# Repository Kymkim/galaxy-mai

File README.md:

# galaxy-mai

This project aims to create a AstroDx controller for the Samsung Galaxy Tab

Cooking in progress! Here are some devlogs!

## 01/01/2026: My 3D printer is back!
Few weeks ago I broke my printer so I had to postpone this project for some weeks. I got a new one now so I should be able to hop back into action. Right now I'm in the process of designining the case. Since the design is pretty much constraied by size, I had to draft the case first to get a better idea on how much space I can have once I start putting down the parts in. 

I'm thinking of creating a PCB for this design and some Khail hotswap sockets. They are easy enough to source and should be low profile enough so it looks somewhat proportional to the actual cab. Yes the PCB of course will add up to the overall cost if someone needs to build this instead of just using generic Omron switches - but my reasoning to this is that I want this to be as compact and integrated as possible. 

The schematic and the code of this project is very basic and pretty much just a simple keyboard hid. I have bunch of codes that I have made prior to this project that should let me just reuse the same code and call it the day.

Anyways, I'll keep working on the case and hopefully get something finished and done in one or two weeks

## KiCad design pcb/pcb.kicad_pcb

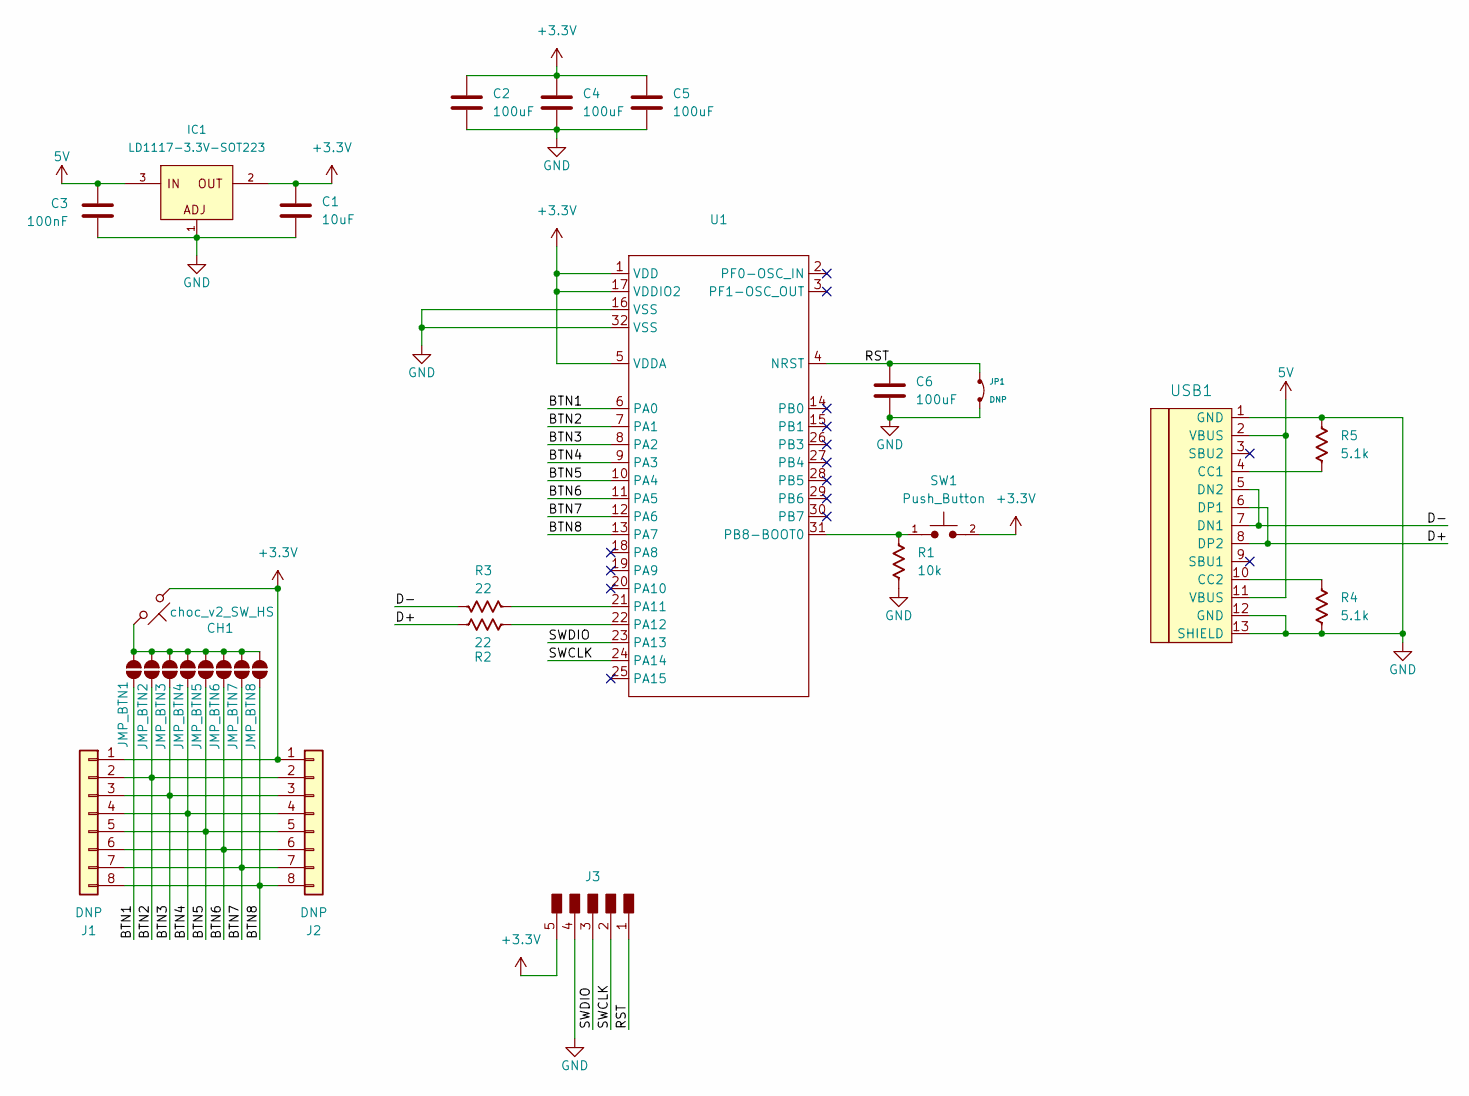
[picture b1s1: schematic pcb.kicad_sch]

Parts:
C1: 10uF; C_0805_2012Metric
C2, C4, C5, C6: 100uF; C_0805_2012Metric
C3: 100nF; C_0805_2012Metric
CH1: choc_v2_SW_HS; SW_Hotswap_Kailh_Choc_V1V2
IC1: LD1117-3.3V-SOT223; SOT223; Part Number LD1117S33CTR
J1, J2: DNP; 1x08_P2.54mm
J3: DNP; PinHeader_01x05_P2.54mm_Vertical_THT_D1.4mm
JMP_BTN1, JMP_BTN2, JMP_BTN3, JMP_BTN4, JMP_BTN5, JMP_BTN6, JMP_BTN7, JMP_BTN8: Jumper_2_NO_NoSilk
JP1: DNP; JUP_P5.08mm
R1: 10k; R_0805_2012Metric
R2, R3: 22; R_0805_2012Metric
R4, R5: 5.1k; R_0805_2012Metric
SW1: Push_Button; SW_PUSH_6mm
U1: LQFP-32_7x7mm_P0.8mm
USB1: HRO-TYPE-C-31-M-12; HRO-TYPE-C-31-M-12-HandSoldering

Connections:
5V: C3.1, IC1.3 (IN), USB1.2 (VBUS), USB1.11 (VBUS)
+3.3V: C1.2, C2.2, C4.2, C5.2, CH1.2, IC1.2 (OUT), J1.1, J2.1, J3.5, SW1.2, U1.1 (VDD), U1.5 (VDDA), U1.17 (VDDIO2); also elsewhere on the board
/BTN1: JMP_BTN1.2 (B), U1.6 (PA0); also elsewhere on the board
/BTN2: J1.2, J2.2, JMP_BTN2.1 (A), U1.7 (PA1); also elsewhere on the board
/BTN3: J1.3, J2.3, JMP_BTN3.1 (A), U1.8 (PA2); also elsewhere on the board
/BTN4: J1.4, J2.4, JMP_BTN4.1 (A), U1.9 (PA3); also elsewhere on the board
/BTN5: J1.5, J2.5, JMP_BTN5.1 (A), U1.10 (PA4); also elsewhere on the board
/BTN6: J1.6, J2.6, JMP_BTN6.1 (A), U1.11 (PA5); also elsewhere on the board
/BTN7: J1.7, J2.7, JMP_BTN7.1 (A), U1.12 (PA6); also elsewhere on the board
/BTN8: J1.8, J2.8, JMP_BTN8.1 (A), U1.13 (PA7); also elsewhere on the board
/D+: R2.1, USB1.6 (DP1), USB1.8 (DP2)
/D-: R3.1, USB1.5 (DN2), USB1.7 (DN1)
/RST: C6.2, J3.1, JP1.1, U1.4 (NRST); also elsewhere on the board
/SWCLK: J3.2, U1.24 (PA14); also elsewhere on the board
/SWDIO: J3.3, U1.23 (PA13); also elsewhere on the board
GND: C1.1, C2.1, C3.2, C4.1, C5.1, C6.1, IC1.1 (ADJ), J3.4, JP1.2, R1.1, R4.2, R5.1, U1.16 (VSS), U1.32 (VSS), USB1.1 (GND), USB1.12 (GND), USB1.13 (SHIELD); also elsewhere on the board
unnamed: CH1.1, JMP_BTN1.1 (A), JMP_BTN2.2 (B), JMP_BTN3.2 (B), JMP_BTN4.2 (B), JMP_BTN5.2 (B), JMP_BTN6.2 (B), JMP_BTN7.2 (B), JMP_BTN8.2 (B)
unnamed 17: R3.2, U1.21 (PA11); also elsewhere on the board
unnamed 18: R2.2, U1.22 (PA12); also elsewhere on the board
unnamed 19: R1.2, SW1.1, U1.31 (PB8-BOOT0); also elsewhere on the board
unnamed: R5.2, USB1.4 (CC1)
unnamed: R4.1, USB1.10 (CC2)

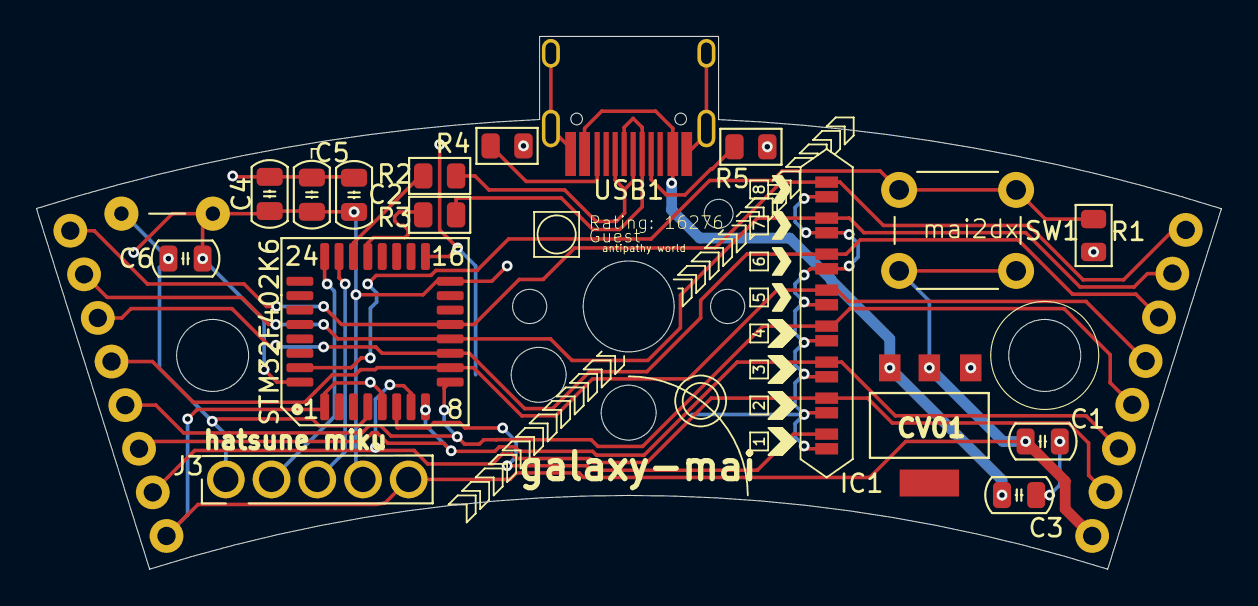
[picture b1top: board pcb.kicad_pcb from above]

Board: 2 copper layers, 65.8 x 29.6 mm, 28 parts (0 on the bottom side), 22 nets.

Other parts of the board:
STM32F402K6: LQFP-32_7x7mm_P0.8mm

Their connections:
+3.3V: STM32F402K6.1 (VDD), STM32F402K6.5 (VDDA), STM32F402K6.17 (VDDIO2); also elsewhere on the board
/BTN1: STM32F402K6.6 (PA0); also elsewhere on the board
/BTN2: STM32F402K6.7 (PA1); also elsewhere on the board
/BTN3: STM32F402K6.8 (PA2); also elsewhere on the board
/BTN4: STM32F402K6.9 (PA3); also elsewhere on the board
/BTN5: STM32F402K6.10 (PA4); also elsewhere on the board
/BTN6: STM32F402K6.11 (PA5); also elsewhere on the board
/BTN7: STM32F402K6.12 (PA6); also elsewhere on the board
/BTN8: STM32F402K6.13 (PA7); also elsewhere on the board
/RST: STM32F402K6.4 (NRST); also elsewhere on the board
/SWCLK: STM32F402K6.24 (PA14); also elsewhere on the board
/SWDIO: STM32F402K6.23 (PA13); also elsewhere on the board
GND: STM32F402K6.16 (VSS), STM32F402K6.32 (VSS); also elsewhere on the board
unnamed 17: STM32F402K6.21 (PA11); also elsewhere on the board
unnamed 18: STM32F402K6.22 (PA12); also elsewhere on the board
unnamed 19: STM32F402K6.31 (PB8-BOOT0); also elsewhere on the board

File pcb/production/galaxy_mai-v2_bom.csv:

Designator,Footprint,Quantity,Value,LCSC Part #
C1,0805,1,10uF,
"C2, C4, C5, C6",0805,4,100uF,
C3,0805,1,100nF,
CH1,SW_Hotswap_Kailh_Choc_V1V2,1,choc_v2_SW_HS,
IC1,SOT223,1,LD1117-3.3V-SOT223,
"JMP_BTN1, JMP_BTN2, JMP_BTN3, JMP_BTN4, JMP_BTN5, JMP_BTN6, JMP_BTN7, JMP_BTN8",Jumper_2_NO_NoSilk,8,~,
R1,0805,1,10k,
"R2, R3",0805,2,22,
"R4, R5",0805,2,5.1k,
STM32F402K6,LQFP-32_7x7mm_P0.8mm,1,~,
SW1,SW_PUSH_6mm,1,Push_Button,
USB1,HRO-TYPE-C-31-M-12-HandSoldering,1,HRO-TYPE-C-31-M-12,

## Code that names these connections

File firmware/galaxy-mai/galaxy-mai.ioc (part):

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Mcu.Name=STM32F042K(4-6)Tx
Mcu.Package=LQFP32
Mcu.UserName=STM32F042K6Tx
PA0.GPIOParameters=GPIO_PuPd,GPIO_Label
PA0.GPIO_Label=BTN1
PA0.GPIO_PuPd=GPIO_PULLDOWN
PA0.Signal=GPIO_Input
PA1.GPIOParameters=GPIO_PuPd,GPIO_Label
PA1.GPIO_Label=BTN2
PA1.GPIO_PuPd=GPIO_PULLDOWN
PA1.Signal=GPIO_Input
PA11.Mode=Device
PA11.Signal=USB_DM
PA12.Mode=Device
PA12.Signal=USB_DP
PA13.Mode=Serial_Wire
PA13.Signal=SYS_SWDIO
PA14.Mode=Serial_Wire
PA14.Signal=SYS_SWCLK
PA2.GPIOParameters=GPIO_PuPd,GPIO_Label
PA2.GPIO_Label=BTN3
PA2.GPIO_PuPd=GPIO_PULLDOWN
PA2.Signal=GPIO_Input
PA3.GPIOParameters=GPIO_PuPd,GPIO_Label
PA3.GPIO_Label=BTN4
PA3.GPIO_PuPd=GPIO_PULLDOWN
PA3.Signal=GPIO_Input
PA4.GPIOParameters=GPIO_PuPd,GPIO_Label
PA4.GPIO_Label=BTN5
PA4.GPIO_PuPd=GPIO_PULLDOWN
PA4.Signal=GPIO_Input
PA5.GPIOParameters=GPIO_PuPd,GPIO_Label
PA5.GPIO_Label=BTN6
PA5.GPIO_PuPd=GPIO_PULLDOWN
PA5.Signal=GPIO_Input
PA6.GPIOParameters=GPIO_PuPd,GPIO_Label
PA6.GPIO_Label=BTN7
PA6.GPIO_PuPd=GPIO_PULLDOWN
PA6.Signal=GPIO_Input
PA7.GPIOParameters=GPIO_PuPd,GPIO_Label
PA7.GPIO_Label=BTN8
PA7.GPIO_PuPd=GPIO_PULLDOWN
PA7.Signal=GPIO_Input
RCC.SYSCLKFreq_VALUE=48000000
RCC.SYSCLKSource=RCC_SYSCLKSOURCE_HSI48
board=custom

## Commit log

2025-12-03 init
2025-12-03 worked on buttons design
2025-12-08 baseplate
2025-12-08 reup
2025-12-08 topshefl work
2025-12-10 top plate addition
2025-12-27 Update README with hiatus note
    Added hiatus note about 3D printer issue.
2026-01-01 revised 3d model
2026-01-01 readme update devlog
2026-01-01 devlogged: Update README with project description
2026-01-03 pcb stuff
2026-01-06 some schematic changes
2026-01-07 making a curved pcb was a mistake, why did i angled this
2026-01-08 pcb revise
2026-01-09 pcb drc factoring pending
2026-01-10 drc resolved pcb ordered
2026-01-16 revised pcb because im a dummy and put the wrong mcu size
2026-01-19 beta firmware
2026-02-06 lots of messages
